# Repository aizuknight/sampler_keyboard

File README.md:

# sampler_keyboard

**sampler_keyboard** is a keyboard with 6 keys to learn the basics of custom built keyboard design.

## Bill of Materials

| Part | Quantity | Purchase |
| ---- | -------- | -------- |
| Seeed Studio XIAO RP2040 | 1 | https://akizukidenshi.com/catalog/g/g117044/, https://www.marutsu.co.jp/pc/i/2229736/ |
| Cherry compatible switch | 6 | https://shop.yushakobo.jp/collections/cherry-mx-clone |
| Switch socket | 6 | https://www.marutsu.co.jp/pc/i/40769481/, https://shop.yushakobo.jp/products/a01ps |
| PCB | 1 | Order at [JLCPCB](https://cart.jlcpcb.com/quote) |
| SK6812MINI-E | 6 | https://akizukidenshi.com/catalog/g/g115478/, https://shop.yushakobo.jp/products/sk6812mini-e-10 |
| 1N4148W | 6 | https://akizukidenshi.com/catalog/g/g107084/, https://www.marutsu.co.jp/pc/i/41883574/, https://shop.yushakobo.jp/products/a0800di-02-100 |
| M2 spacer (4mm) | 8 | https://shop.yushakobo.jp/products/a0800r2?variant=37665433944225, https://shop.yushakobo.jp/products/a0800c2?variant=37665435123873 |
| M2 screw (5mm) | 4 | https://shop.yushakobo.jp/products/a0800b2?variant=37665433321633 |
| M2 screw (8mm) | 4 | https://shop.yushakobo.jp/products/8006?variant=47615864963303, https://shop.yushakobo.jp/products/a0800n2?variant=37665433026721 |
| Switch plate (1mm thick) | 1 | Buy an acrylic panel at [hazaiya](https://www.hazaiya.co.jp/) and cut by yourself |
| Base plate (3mm thick) | 1 | Buy an acrylic panel at [hazaiya](https://www.hazaiya.co.jp/) and cut by yourself |

## How to Build Firmware

> [!NOTE]
> **If you are going to build the firmware on CentOS in AINS (University of Aizu), go straight to step 2.**

> [!TIP]
> **I recommend you to build the firmware on CentOS in the AINS (University of Aizu) if you are a beginner. You can SSH into CentOS server just by `ssh s13XXXXX@linsv.u-aizu.ac.jp` while connected to the AINS network.**

### 1. Prepare Docker Engine

If Docker is already installed and it can be run without `sudo`, go straight to step 2. The build script uses Docker. If Docker is not installed yet, install Docker Engine on your Linux system (including WSL):

```bash
curl -fsSL https://get.docker.com | sudo sh
```

If `docker` cannot be run without `sudo`, add your user to `docker` group:

```bash
sudo usermod -aG docker $USER
```

> [!NOTE]
> For the user group changes to take effect, you will need to log out. You might need to reboot your computer instead of logging out for the user group changes to take effect.

These commands require `curl` and permission to install system software.

### 2. Clone Repository

```
git clone https://github.com/aizuknight/sampler_keyboard.git
cd sampler_keyboard/
```

This command requires `git` to be installed.

### 3. Build Firmware

After cloning the repository, run the command below from the repository root (You should be there already) for your chosen keymap. The script prepares the build environment and compiles the firmware.

> [!WARNING]
> You need at least 6.16 GB of disk space with Docker.

> [!NOTE]
> The first build requires internet access and takes longer because the script automatically builds the QMK container image (about 4 minutes with Docker on Intel Core i5-12400). Later builds reuse the image.

> [!NOTE]
> When you build the firmware on CentOS in the AINS (University of Aizu), you may build the QMK container image all the time unless you frequently build the firmware. Since the script uses `/tmp/` directory to store the QMK container image (9.6 GB), the stored data will be deleted without frequent access. If you do not like that, you can manually set the location to store the QMK container image with environment variable `PODMAN_STRAGE_DIRECTORY` (Advanced).

#### Option 1: Build the Default Keymap

```bash
./firmware/build.sh
```

The built firmware is located at `firmware/output/sampler_keyboard_default.uf2`.

#### Option 2: Build Firmware with VIA Compatibility

```bash
./firmware/build.sh via
```

The built firmware is located at `firmware/output/sampler_keyboard_via.uf2`.

## How to Install Firmware to The Keyboard

1. Connect Seeed Studio XIAO RP2040 to your computer with USB cable **while pressing reset button on the Seeed Studio XIAO RP2040**.
2. Release the reset button on the Seeed Studio XIAO RP2040.
3. Drag and drop the firmware to the USB mass strage device named "RPI-RP2".

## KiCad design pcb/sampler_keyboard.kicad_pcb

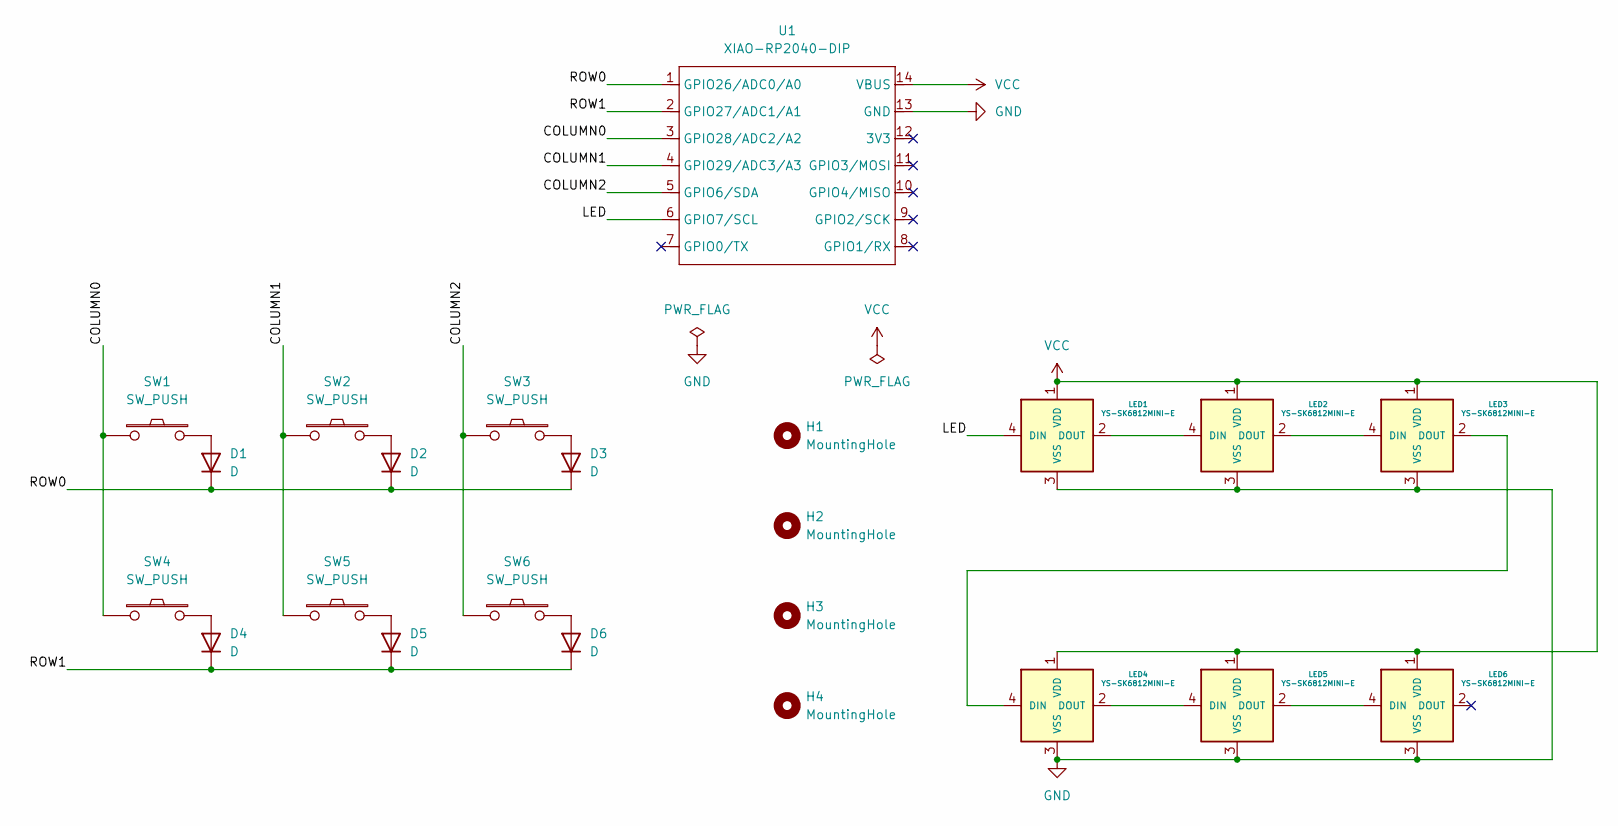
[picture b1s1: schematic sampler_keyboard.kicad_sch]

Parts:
D1, D2, D3, D4, D5, D6: D; D3_SMD_v2
H1, H2, H3, H4: MountingHole; MountingHole_2.2mm_M2
LED1, LED2, LED3, LED4, LED5, LED6: YS-SK6812MINI-E
SW1, SW2, SW3, SW4, SW5, SW6: SW_PUSH; CherryMX_Hotswap
U1: XIAO-RP2040-DIP

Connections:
/COLUMN0: SW1.1, SW4.1, U1.3 (GPIO28/ADC2/A2)
/COLUMN1: SW2.1, SW5.1, U1.4 (GPIO29/ADC3/A3)
/COLUMN2: SW3.1, SW6.1, U1.5 (GPIO6/SDA)
/LED: LED1.4 (DIN), U1.6 (GPIO7/SCL)
/ROW0: D1.1 (K), D2.1 (K), D3.1 (K), U1.1 (GPIO26/ADC0/A0)
/ROW1: D4.1 (K), D5.1 (K), D6.1 (K), U1.2 (GPIO27/ADC1/A1)
GND: LED1.3 (VSS), LED2.3 (VSS), LED3.3 (VSS), LED4.3 (VSS), LED5.3 (VSS), LED6.3 (VSS), U1.13 (GND)
unnamed: D1.2 (A), SW1.2
unnamed: D2.2 (A), SW2.2
unnamed: D3.2 (A), SW3.2
unnamed: D4.2 (A), SW4.2
unnamed: D5.2 (A), SW5.2
unnamed: D6.2 (A), SW6.2
unnamed: LED1.2 (DOUT), LED2.4 (DIN)
unnamed: LED2.2 (DOUT), LED3.4 (DIN)
unnamed: LED3.2 (DOUT), LED4.4 (DIN)
unnamed: LED4.2 (DOUT), LED5.4 (DIN)
unnamed: LED5.2 (DOUT), LED6.4 (DIN)
VCC: LED1.1 (VDD), LED2.1 (VDD), LED3.1 (VDD), LED4.1 (VDD), LED5.1 (VDD), LED6.1 (VDD), U1.14 (VBUS)

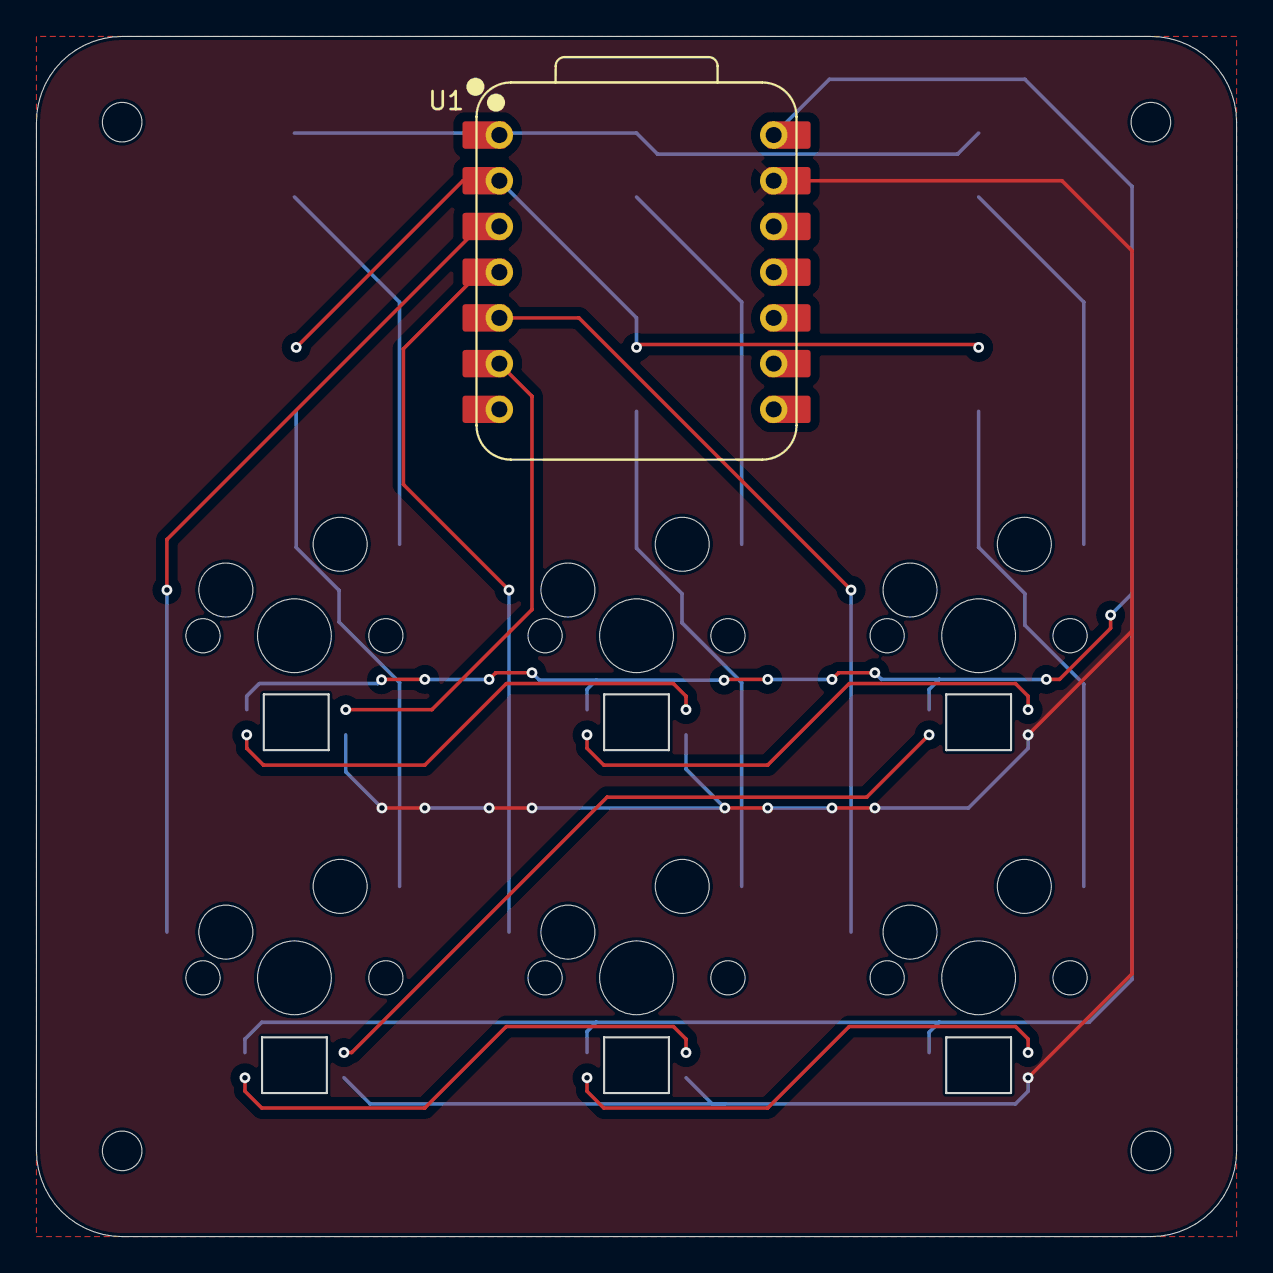
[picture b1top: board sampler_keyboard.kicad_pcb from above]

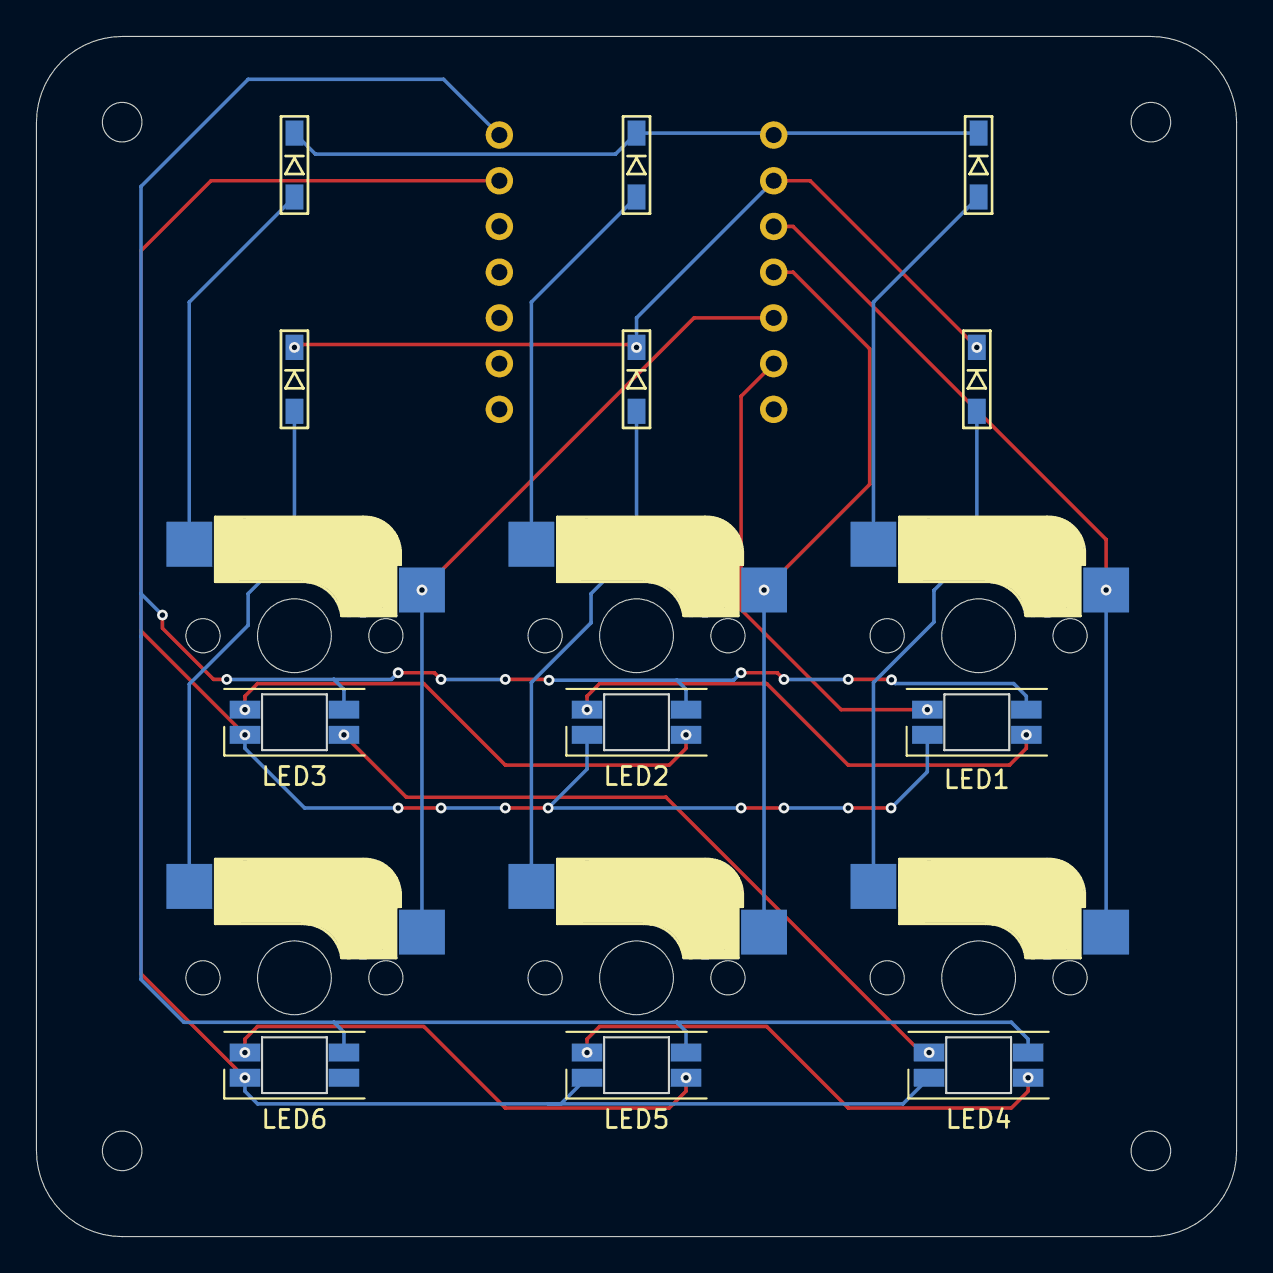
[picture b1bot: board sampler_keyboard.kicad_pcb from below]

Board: 2 copper layers, 66.6 x 66.6 mm, 23 parts (12 on the bottom side), 19 nets.

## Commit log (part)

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2026-06-03 Add firmware source code and build script
